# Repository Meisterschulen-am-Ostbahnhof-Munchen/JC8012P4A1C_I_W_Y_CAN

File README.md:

# JC8012P4A1C Enclosure & CAN Addon System

Enclosure, mounting and CAN/Power addon board for the Guition JC8012P4A1C (ESP32-P4, 10.1")
display, used by [espVT](https://github.com/Meisterschulen-am-Ostbahnhof-Munchen/espVT).

The system integrates an ISOBUS/CAN interface, 12 V power supply, a 3D-printed enclosure frame,
and an FR4 backplate with VESA 100 mount and speaker. An optional second variant extends the unit
with a 12-key tactile keypad next to the display.

**Online:** interactive BOMs, schematics and drawings at
<https://meisterschulen-am-ostbahnhof-munchen.github.io/JC8012P4A1C_I_W_Y_CAN/>

More renderings and how they are made: [assembly/render/](assembly/render/README.md).

## Repository Structure

The project is structured into PCBs, mechanics and final assembly:

```text
JC8012P4A1C_I_W_Y_CAN/
├── pcbs/
│   ├── can_power/        # CAN-Bus & 12V/5V power supply addon board
│   ├── backplate/        # FR4 backplate with VESA 100 mount & speaker grille (variant 1)
│   ├── backplate_keypad/ # Widened FR4 backplate for variant 2 (with keypad)
│   └── keypad/           # 12-key tactile keypad PCB (variant 2)
├── mechanics/            # 3D printed frame designs (FreeCAD scripts, STL & STEP files)
├── assembly/             # Assembly drawings (A3 PDF), 3D render models & assembly scripts
├── assembly_bom.csv      # Complete mechanical parts, fasteners & cables BOM
├── mouser_order.csv      # Ordering list for non-Würth components
└── README.md
```

## Variants

| Component | Variant 1 (Standard) | Variant 2 (with Keypad) |
|---|---|---|
| Display | Guition JC8012P4A1C (10.1" ESP32-P4) | Guition JC8012P4A1C (10.1" ESP32-P4) |
| CAN / Power Board | [`pcbs/can_power/`](pcbs/can_power/README.md) | [`pcbs/can_power/`](pcbs/can_power/README.md) |
| Frame | `mechanics/frame.stl` | `mechanics/frame_keypad.stl` |
| Backplate | [`pcbs/backplate/`](pcbs/backplate/README.md) | [`pcbs/backplate_keypad/`](pcbs/backplate_keypad/README.md) (296.9 mm wide) |
| Keypad | — | [`pcbs/keypad/`](pcbs/keypad/README.md) (12 tactile keys F1–F12) |
| Assembly Drawing | [assembly/JC8012P4A1C_assembly_variant1.pdf](assembly/JC8012P4A1C_assembly_variant1.pdf) | [assembly/JC8012P4A1C_assembly_variant2_keypad.pdf](assembly/JC8012P4A1C_assembly_variant2_keypad.pdf) |

Details on mechanics: [mechanics/README.md](mechanics/README.md).  
Details on assembly: [assembly/README.md](assembly/README.md).

## Bills of Materials (BOM)

| BOM | File |
|---|---|
| CAN & Power board | [pcbs/can_power/production/JC8012P4A1C_I_W_Y_CAN_bom.csv](pcbs/can_power/production/JC8012P4A1C_I_W_Y_CAN_bom.csv) |
| Back plate (variant 1) | [pcbs/backplate/production/JC8012P4A1C_backplate_bom.csv](pcbs/backplate/production/JC8012P4A1C_backplate_bom.csv) |
| Back plate (variant 2, keypad) | [pcbs/backplate_keypad/production/JC8012P4A1C_backplate_keypad_bom.csv](pcbs/backplate_keypad/production/JC8012P4A1C_backplate_keypad_bom.csv) |
| Keypad (variant 2) | [pcbs/keypad/production/JC8012P4A1C_keypad_bom.csv](pcbs/keypad/production/JC8012P4A1C_keypad_bom.csv) |
| Final assembly (mechanical fasteners, cables) | [assembly_bom.csv](assembly_bom.csv) |
| Parts to order at Mouser (all non-Würth parts) | [mouser_order.csv](mouser_order.csv) |

### Interactive HTML BOMs (Assembly Checklists)

For manual assembly, interactive HTML BOMs (with checkboxes for soldering and inspection) are provided:

| Board | Interactive BOM |
|---|---|
| CAN & Power board | [pcbs/can_power/production/JC8012P4A1C_I_W_Y_CAN_ibom.html](pcbs/can_power/production/JC8012P4A1C_I_W_Y_CAN_ibom.html) |
| Back plate | [pcbs/backplate/production/JC8012P4A1C_backplate_ibom.html](pcbs/backplate/production/JC8012P4A1C_backplate_ibom.html) |
| Back plate (keypad variant) | [pcbs/backplate_keypad/production/JC8012P4A1C_backplate_keypad_ibom.html](pcbs/backplate_keypad/production/JC8012P4A1C_backplate_keypad_ibom.html) |
| Keypad | [pcbs/keypad/production/JC8012P4A1C_keypad_ibom.html](pcbs/keypad/production/JC8012P4A1C_keypad_ibom.html) |

## Manufacturing

Each PCB folder in `pcbs/` contains its complete KiCad 10 project, local component libraries (`lib/`), documentation (`docs/`), and fabrication outputs (`production/`).
See the respective README files in [`pcbs/can_power/`](pcbs/can_power/README.md), [`pcbs/backplate/`](pcbs/backplate/README.md), [`pcbs/backplate_keypad/`](pcbs/backplate_keypad/README.md), and [`pcbs/keypad/`](pcbs/keypad/README.md) for generation commands and specifications.

The 3D-printable frame is generated using FreeCAD scripts in [`mechanics/`](mechanics/README.md).

## Licence

- Schematics, PCB layouts, scripts and documentation: GPL-3.0 ([LICENSE](LICENSE)).
- `pcbs/*/lib/` and `assembly/models/`: symbols, footprints and 3D models from the Würth Elektronik eiSos libraries, licensed CC BY-SA 4.0 with the Würth exception for designs that use them (see `Wurth_Disclaimer_READ_ME.txt` in these folders).
- Footprints and 3D models from the KiCad standard libraries: CC BY-SA 4.0 with the KiCad exception.
- `mechanics/`: derivative of a Thingiverse design by 8bitmcu, CC BY-SA, see [mechanics/LICENSE.md](mechanics/LICENSE.md).

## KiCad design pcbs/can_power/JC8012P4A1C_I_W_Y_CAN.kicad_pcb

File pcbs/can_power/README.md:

# JC8012P4A1C CAN & Power Board

ISOBUS / CAN interface (250 kbit/s) for the Guition JC8012P4A1C (ESP32-P4, 10.1")
display, used by [espVT](https://github.com/Meisterschulen-am-Ostbahnhof-Munchen/espVT).
The board is mounted on the back of the display board and powered from the 12 V
board net. It also supplies 5 V to the display board.

KiCad 10 project. Project-local libraries are in `lib/`.

Top view: [docs/board_3d_top.png](docs/board_3d_top.png)

## Connections

| Connector | Part | Purpose |
|---|---|---|
| J1 | Würth WR-PHD 610110249121 (2×5 pin header, SMT, right angled) | ribbon cable to IDC D-Sub 9 female Würth 618009221923 |
| J2 | Würth WR-FPC 68711414522 (14 pin, 0.5 mm) | FFC to FPC3 "EXTEND1" of the display board |
| J3 | Würth WR-WTB 653104131822 (4 pin, 1.25 mm) | 5 V to CN2 of the display board |

### D-Sub 9 (via ribbon cable on J1)

Pinout of the Müller-Elektronik BASIC-Terminal CAN-ISO connector. It fits the
adapter cable 481595 (D-Sub 9 male to In-Cab CPC-9 female).

| D-Sub | J1 | Signal |
|---|---|---|
| 1 | 1 | CAN_L |
| 2 | 3 | CAN_L |
| 3 | 5 | TBC_GND (see R8) |
| 4 | 7 | CAN_H |
| 5 | 9 | TBC_PWR_in (not used) |
| 6 | 2 | ECU_GND |
| 7 | 4 | CAN_H |
| 8 | 6 | TBC_PWR_out |
| 9 | 8 | ECU_PWR (12 V board net) |
| – | 10 | not used |

CAN_L (1/2) and CAN_H (4/7) are connected on the board to loop the bus through.

**Polarisation:** J1 has no shroud (an 8 mm high part is the maximum under
the cover, a box header with IDC socket would be too high). To prevent the
IDC socket from being plugged in turned by 180°, cut off pin 10 of J1 and
close position 10 of the IDC socket with a coding plug. Pin 10 is marked
"cut" on the silkscreen. Pins 9 and 10 are
not used. Plugged in turned, the bus TBC_PWR and ECU_PWR (12 V) would end up
on the board GND and CAN_L.

## Mechanics

- All parts on the top side (SMT only), nothing on the bottom side
- Stack height: cover 14 mm − display board 1.5 mm − M2 standoffs 3 mm −
  addon board 1.5 mm ≈ 8 mm free above the addon board
- Fixing on the 58 × 46 mm grid of the display board standoffs S1–S4
  (H1 = S1, H2 = S4, H3 = S2, H4 = S3): SMD steel spacers Würth WA-SMST
  9774025943R (L 2.5 mm, through hole 2.25 mm), land pattern as in the
  datasheet: 5.3 mm GND pad on top, 3.0 mm **non-plated** hole for the
  Ø 2.8 × 1.4 mm collar of the spacer. The DRC rule in
  `JC8012P4A1C_I_W_Y_CAN.kicad_dru` allows the pad right up to the hole.
- Screws **M2×6**, without washer: spacer 2.5 mm + PCB 1.6 mm leaves 1.9 mm
  thread engagement in the 2.5 mm deep blind thread of S1–S4. M2×8 would
  bottom out.
- Notches for CN5 (pin header), the 100 µF capacitor next to S4 and the
  CR1220 RTC holder of the display board

### FPC3 (J2)

| Pin | Signal |
|---|---|
| 1, 2 | GND |
| 7 | CAN_RXD (GPIO5) |
| 8 | CAN_TXD (GPIO4) |
| 9 | CAN_NEN (GPIO3, 10k pull-down: transceiver active by default) |
| 13, 14 | +3V3 (VDDA, transceiver VIO) |

FFC: 14 pin, 0.5 mm pitch, **type B (contacts on opposite sides)**.
The cable leaves FPC3 towards the board edge, makes one 180° turn and enters
J2 from the edge of the addon board. Both connectors are bottom-contact ZIF
with the same orientation (opening towards the edge, pin 1 on the right
side seen from the back of the display, next to the TF card), so pin 1
connects to pin 1. A type A cable would have its contacts facing up at J2;
turning it over to make it fit reverses the pin order and swaps GND (1/2)
and 3V3 (13/14).

## Termination

ISO 11783-2 ECU Type I WEAK: split termination 750 Ω + 750 Ω with 47 nF to GND.

## TBC power output and R8

Like the BASIC-Terminal, the board supplies power for the terminating bias
circuits (TBC) on D-Sub pin 8 (TBC_PWR_out): board net minus about 0.4 V
(Schottky diode D4), limited by PTC F2 (0.14 A). Some harnesses do not start
without it.

**R8 (0 Ω, TBC_GND to GND) is not fitted (DNP) by default.** This keeps
TBC_GND isolated, which is the compatible default. If a harness needs a
TBC_GND return for its terminator, fit R8 with a 0 Ω resistor (0603).

## Power

- 12 V board net only (ECU_PWR), fuse F1 1 A slow
- Bidirectional TVS Würth 824551241 (SMDJ24CA), clamping ≤ 38.9 V
- Reverse polarity protection: dual P-MOSFET Vishay Si4948BEY (SO-8), both
  halves in parallel, 15 V gate zener. Drop-in for the KiCad symbol
  DMP6050SSD (same SO-8 pinout S1 G1 S2 G2 D2 D2 D1 D1), which is used as
  the schematic symbol.
- Buck converter Würth MagI³C 171030601: 5 V / 3 A for the transceiver and the display board

## Test points

SMD pads (1.5 mm), labelled with the net name on the silkscreen:

| TP | Net | Position |
|---|---|---|
| TP1 | +5V | next to J3 |
| TP2 | GND | next to J3 |
| TP3 | CAN_H | between D1 and J1 |
| TP4 | CAN_L | between D1 and J1 |
| TP5 | VIN_PROT (12 V after fuse and reverse polarity protection) | right of C13, below L2 |

## PCB

66 × 54 mm, 1.6 mm, 6 layers:

| Layer | Use |
|---|---|
| F.Cu | all parts and signals, GND pour, local pours for VIN_PROT, VIN_BUCK and +5V |
| In1.Cu | GND plane |
| In2.Cu | +5V plane |
| In3.Cu | GND plane (also balances the copper of In2) |
| In4.Cu | GND plane |
| B.Cu | GND plane, one short signal (CAN_NEN) |

- Vias 0.5 mm / 0.3 mm drill (a 0.2 mm drill costs extra at JLCPCB). Many vias are placed in SMD pads (GND and
  +5V pads, 77 thermal vias under the exposed pad of U2), so the vias
  **must be epoxy filled and capped** (via-in-pad). Without this, solder
  is drawn into the holes during reflow.
- GND stitching vias on a 4 mm grid connect all GND layers.
- Pours connect solid to SMD pads and to the spacer pads H1–H4 (reflow
  soldering, a hand soldering iron will not heat them).
- Net classes: Power 0.8 mm (12 V path and +5V), CAN 0.3 mm, Default 0.25 mm.

## Manufacturing

The current Gerber and drill files are in the zip
`production/JC8012P4A1C_I_W_Y_CAN_gerber.zip` (ready for upload), the BOM
in `production/JC8012P4A1C_I_W_Y_CAN_bom.csv`. Make them again after changes
to the board: in KiCad PCB editor → File → Fabrication Outputs → Gerbers and
Drill Files, or from the command line:

```sh
kicad-cli pcb export gerbers -o production/gerber -l F.Cu,In1.Cu,In2.Cu,In3.Cu,In4.Cu,B.Cu,F.Paste,B.Paste,F.Silkscreen,B.Silkscreen,F.Mask,B.Mask,Edge.Cuts --subtract-soldermask --no-x2 --no-netlist --check-zones JC8012P4A1C_I_W_Y_CAN.kicad_pcb
kicad-cli pcb export drill -o production/gerber/ --format excellon --excellon-units mm --excellon-separate-th JC8012P4A1C_I_W_Y_CAN.kicad_pcb
```

Zip the content of `production/gerber` (the folder itself is not in the
repository) to `production/JC8012P4A1C_I_W_Y_CAN_gerber.zip` and upload it (e.g. JLCPCB:
6 layers, 1.6 mm, via covering "Epoxy Filled & Capped").

Interactive HTML BOM:

```sh
python generate_interactive_bom.py --no-browser --dest-dir production --name-format "%f_ibom" --include-tracks --include-nets --highlight-pin1 all --checkboxes "Gelötet,Kontrolliert" --mark-when-checked "Gelötet" --show-fields "Value,Footprint,MPN" --group-fields "Value,Footprint,MPN" --extra-fields "MPN" --dnp-field kicad_dnp --bom-view left-right --layer-view F --show-fabrication JC8012P4A1C_I_W_Y_CAN.kicad_pcb
```

BOM export:

```sh
kicad-cli sch export bom -o production/JC8012P4A1C_I_W_Y_CAN_bom.csv --fields "Reference,QUANTITY,Value,Manufacturer,MPN,Footprint,DNP" --labels "Reference,Qty,Value,Manufacturer,MPN,Footprint,DNP" --group-by "Value,Footprint,MPN,Manufacturer,DNP" JC8012P4A1C_I_W_Y_CAN.kicad_sch
```

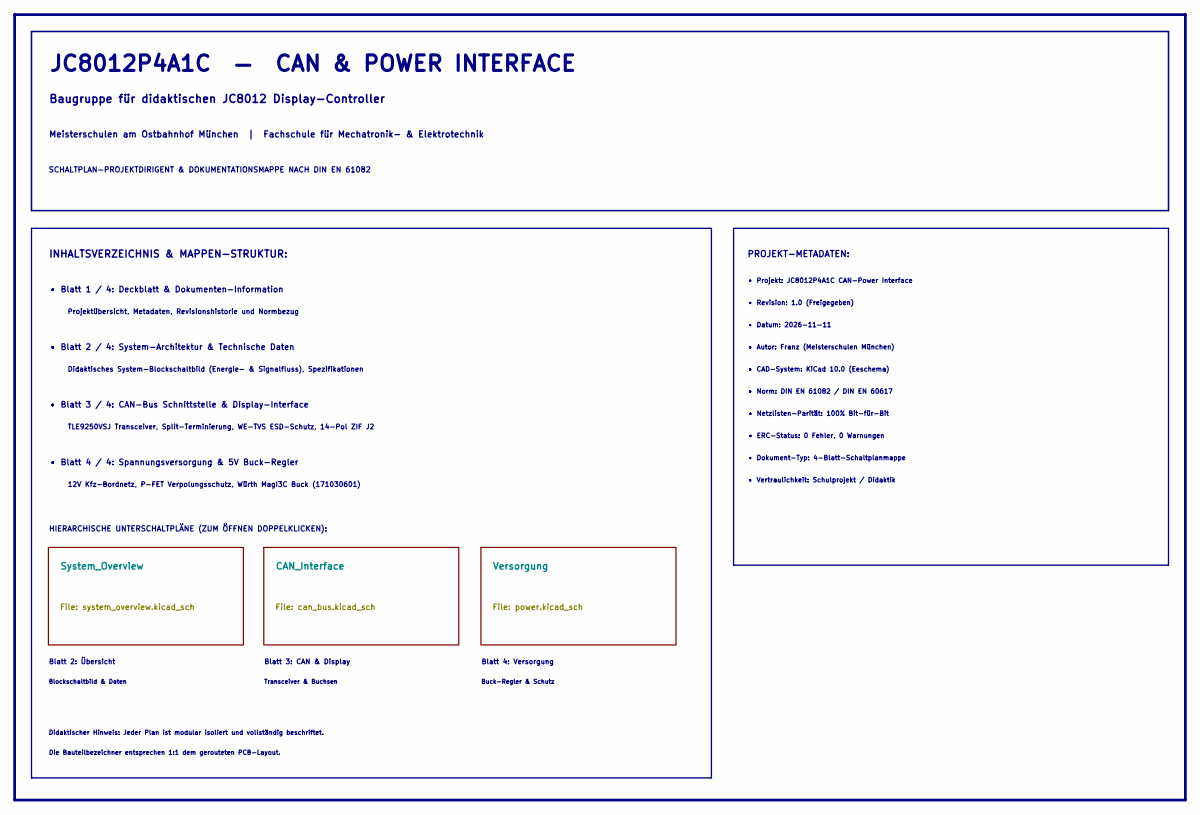
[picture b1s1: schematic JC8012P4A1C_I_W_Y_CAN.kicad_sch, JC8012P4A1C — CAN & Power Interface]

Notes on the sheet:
Projektübersicht, Metadaten, Revisionshistorie und Normbezug
12V Kfz-Bordnetz, P-FET Verpolungsschutz, Würth MagI3C Buck (171030601)
Blatt 2: Übersicht
• CAD-System: KiCad 10.0 (Eeschema)
• Revision: 1.0 (Freigegeben)
HIERARCHISCHE UNTERSCHALTPLÄNE (ZUM ÖFFNEN DOPPELKLICKEN):
Didaktisches System-Blockschaltbild (Energie- & Signalfluss), Spezifikationen
• Netzlisten-Parität: 100% Bit-für-Bit
PROJEKT-METADATEN:
Meisterschulen am Ostbahnhof München | Fachschule für Mechatronik- & Elektrotechnik
• Norm: DIN EN 61082 / DIN EN 60617
• Blatt 3 / 4: CAN-Bus Schnittstelle & Display-Interface
Baugruppe für didaktischen JC8012 Display-Controller
• Dokument-Typ: 4-Blatt-Schaltplanmappe
• ERC-Status: 0 Fehler, 0 Warnungen
Blatt 4: Versorgung
INHALTSVERZEICHNIS & MAPPEN-STRUKTUR:
• Blatt 4 / 4: Spannungsversorgung & 5V Buck-Regler
Buck-Regler & Schutz
• Blatt 2 / 4: System-Architektur & Technische Daten
Blatt 3: CAN & Display
Blockschaltbild & Daten
SCHALTPLAN-PROJEKTDIRIGENT & DOKUMENTATIONSMAPPE NACH DIN EN 61082
• Datum: 2026-11-11
• Vertraulichkeit: Schulprojekt / Didaktik
JC8012P4A1C — CAN & POWER INTERFACE
• Blatt 1 / 4: Deckblatt & Dokumenten-Information
Die Bauteilbezeichner entsprechen 1:1 dem gerouteten PCB-Layout.
Transceiver & Buchsen
TLE9250VSJ Transceiver, Split-Terminierung, WE-TVS ESD-Schutz, 14-Pol ZIF J2
Didaktischer Hinweis: Jeder Plan ist modular isoliert und vollständig beschriftet.
• Autor: Franz (Meisterschulen München)
• Projekt: JC8012P4A1C CAN-Power Interface

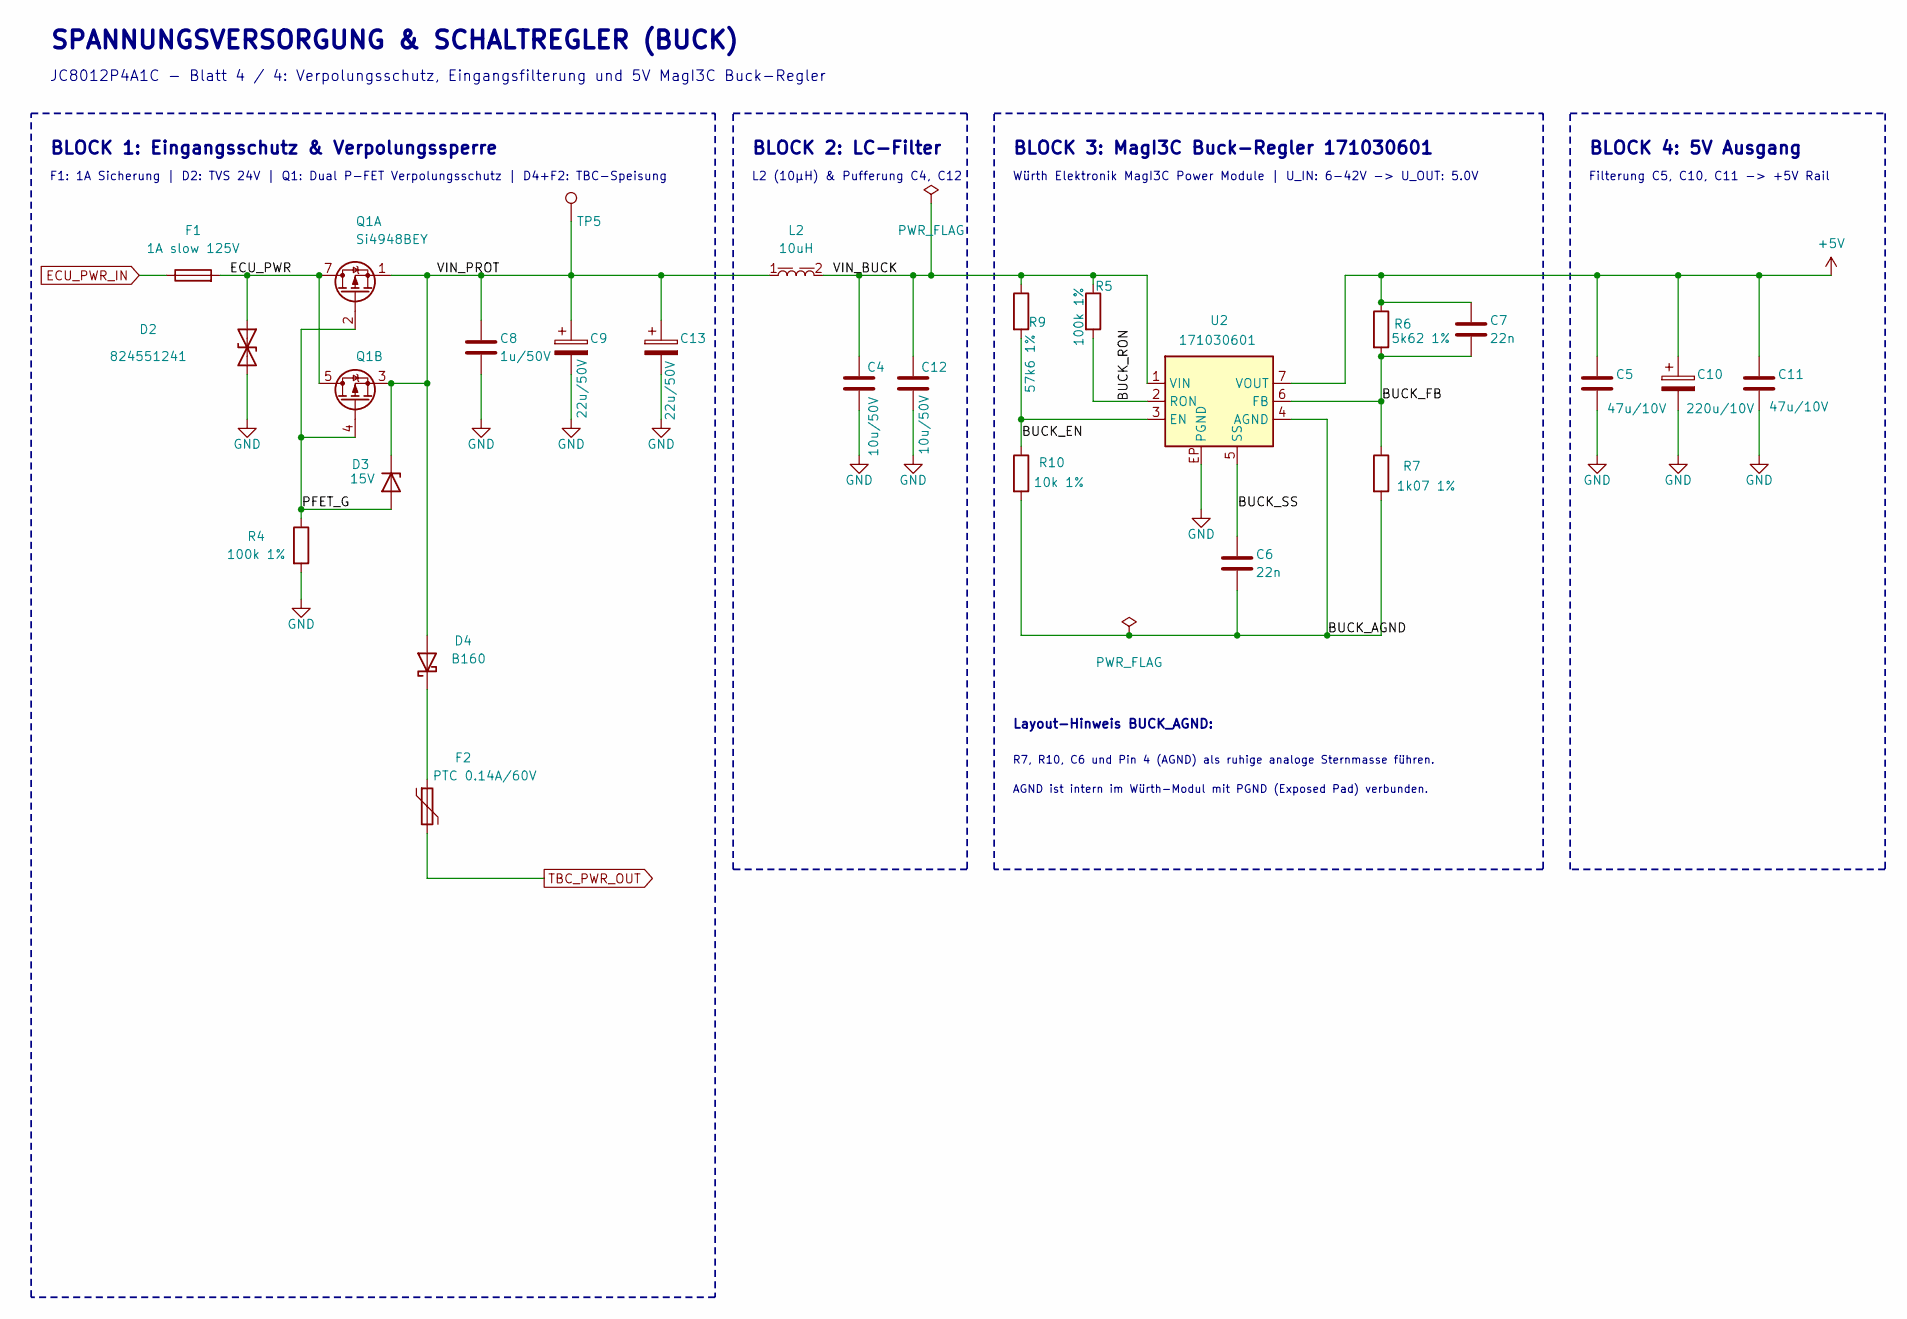
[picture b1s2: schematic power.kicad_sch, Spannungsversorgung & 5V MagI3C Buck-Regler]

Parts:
C4, C12: 10u/50V; C_1210_3225Metric; MPN 885012209073
C5, C11: 47u/10V; C_1210_3225Metric; MPN 885012109007
C6, C7: 22n; C_0603_1608Metric; MPN 885012206091
C8: 1u/50V; C_1210_3225Metric; MPN 885012209047
C9, C13: 22u/50V; CP_Wurth_WCAP-ASLI-D6.3L5.5; MPN 865080643008
C10: 220u/10V; CP_Wurth_WCAP-PSLP-D6.3L5.8; MPN 875105244013
D2: 824551241; D_Wurth_WE-TVSP-DO214-AB-3000W_BI; MPN 824551241
D3: 15V; D_SOD-123; MPN MMSZ5245B_R1_00001
D4: B160; D_SMA; MPN B160-13-F
F1: 1A slow 125V; Fuse_Littelfuse-NANO2-451_453; MPN 0452001.MRL
F2: PTC 0.14A/60V; Fuse_1812_4532Metric; MPN MF-MSMF014-2
L2: 10uH; L_Wurth_WE-PD2-5848; MPN 74477410
Q1: Si4948BEY; SOIC-8_3.9x4.9mm_P1.27mm; MPN SI4948BEY-T1-E3
R4, R5: 100k 1%; R_0603_1608Metric; MPN RC0603FR-07100KL
R6: 5k62 1%; R_0603_1608Metric; MPN RC0603FR-075K62L
R7: 1k07 1%; R_0603_1608Metric; MPN RC0603FR-071K07L
R9: 57k6 1%; R_0603_1608Metric; MPN RC0603FR-0757K6L
R10: 10k 1%; R_0603_1608Metric; MPN RC0603FR-0710KL
TP5: VIN_PROT; TestPoint_Pad_D1.5mm
U2: 171030601; U_Wurth_WPME-VDRM-TO263-7EP; MPN 171030601

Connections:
+5V: C5.1, C7.1, C10.1, C11.1, R6.1, U2.7 (VOUT); also elsewhere on the board
/Versorgung/BUCK_AGND: C6.2, R7.2, R10.2, U2.4 (AGND)
/Versorgung/BUCK_EN: R9.2, R10.1, U2.3 (EN)
/Versorgung/BUCK_FB: C7.2, R6.2, R7.1, U2.6 (FB)
/Versorgung/BUCK_RON: R5.2, U2.2 (RON)
/Versorgung/BUCK_SS: C6.1, U2.5 (SS)
/Versorgung/ECU_PWR: D2.1 (A1), F1.2, Q1.5 (D2), Q1.6 (D2), Q1.7 (D1), Q1.8 (D1)
/Versorgung/PFET_G: D3.2 (A), Q1.2 (G1), Q1.4 (G2), R4.1
/Versorgung/VIN_BUCK: C4.1, C12.1, L2.2, R5.1, R9.1, U2.1 (VIN)
/Versorgung/VIN_PROT: C8.1, C9.1, C13.1, D3.1 (K), D4.2 (A), L2.1, Q1.1 (S1), Q1.3 (S2), TP5.1 (1_1)
unnamed: D4.1 (K), F2.1
TBC_PWR_OUT: F2.2; also elsewhere on the board

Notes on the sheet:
Würth Elektronik MagI3C Power Module | U_IN: 6-42V -> U_OUT: 5.0V
JC8012P4A1C - Blatt 4 / 4: Verpolungsschutz, Eingangsfilterung und 5V MagI3C Buck-Regler
R7, R10, C6 und Pin 4 (AGND) als ruhige analoge Sternmasse führen.
BLOCK 3: MagI3C Buck-Regler 171030601
BLOCK 4: 5V Ausgang
Layout-Hinweis BUCK_AGND:
AGND ist intern im Würth-Modul mit PGND (Exposed Pad) verbunden.
F1: 1A Sicherung | D2: TVS 24V | Q1: Dual P-FET Verpolungsschutz | D4+F2: TBC-Speisung
BLOCK 1: Eingangsschutz & Verpolungssperre
L2 (10µH) & Pufferung C4, C12
Filterung C5, C10, C11 -> +5V Rail
SPANNUNGSVERSORGUNG & SCHALTREGLER (BUCK)
BLOCK 2: LC-Filter

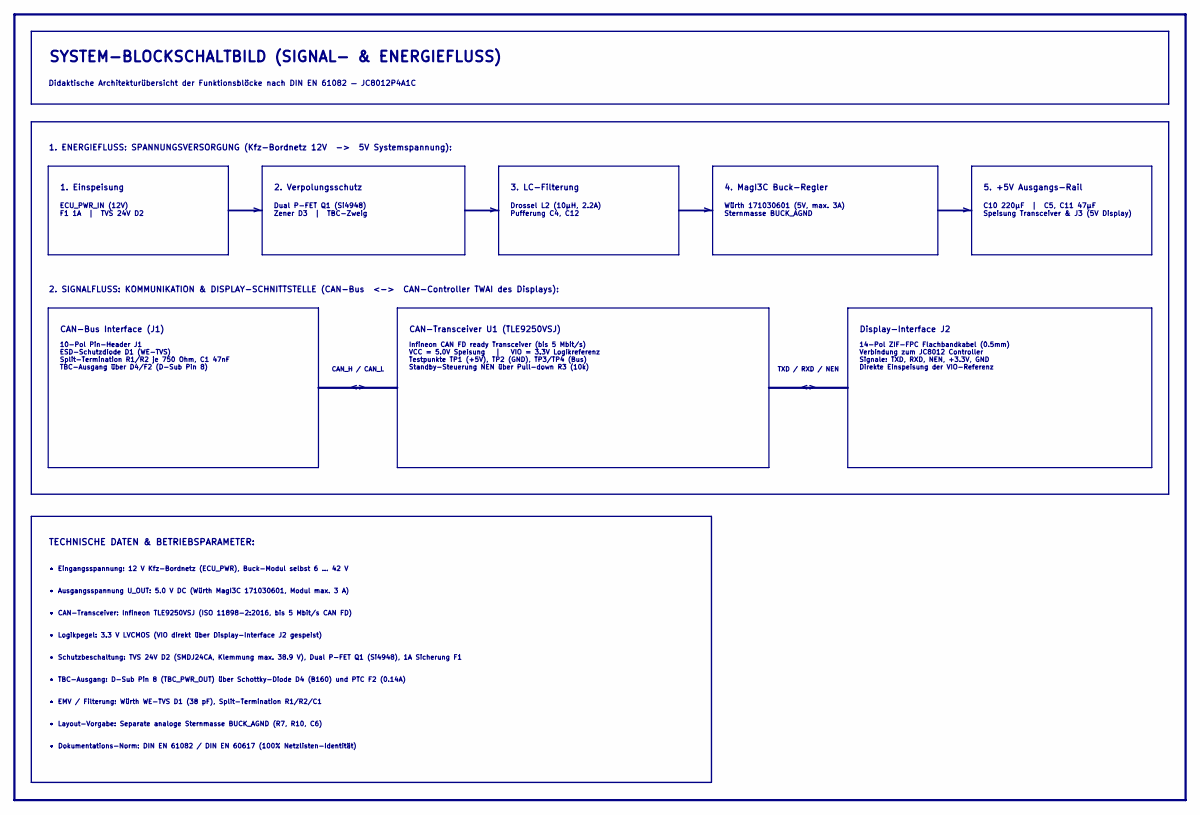
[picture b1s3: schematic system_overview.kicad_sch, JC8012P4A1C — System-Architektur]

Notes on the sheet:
1. Einspeisung
5. +5V Ausgangs-Rail
• Schutzbeschaltung: TVS 24V D2 (SMDJ24CA, Klemmung max. 38.9 V), Dual P-FET Q1 (Si4948), 1A Sicherung F1
TECHNISCHE DATEN & BETRIEBSPARAMETER:
CAN_H / CAN_L
Würth 171030601 (5V, max. 3A) Sternmasse BUCK_AGND
• EMV / Filterung: Würth WE-TVS D1 (38 pF), Split-Termination R1/R2/C1
• Layout-Vorgabe: Separate analoge Sternmasse BUCK_AGND (R7, R10, C6)
• CAN-Transceiver: Infineon TLE9250VSJ (ISO 11898-2:2016, bis 5 Mbit/s CAN FD)
Drossel L2 (10µH, 2.2A) Pufferung C4, C12
Infineon CAN FD ready Transceiver (bis 5 Mbit/s) VCC = 5.0V Speisung | VIO = 3.3V Logikreferenz Testpunkte TP1 (+5V), TP2 (GND), TP3/TP4 (Bus) Standby-Steuerung NEN über Pull-down R3 (10k)
CAN-Transceiver U1 (TLE9250VSJ)
Dual P-FET Q1 (Si4948) Zener D3 | TBC-Zweig
Didaktische Architekturübersicht der Funktionsblöcke nach DIN EN 61082 — JC8012P4A1C
1. ENERGIEFLUSS: SPANNUNGSVERSORGUNG (Kfz-Bordnetz 12V -> 5V Systemspannung):
4. MagI3C Buck-Regler
14-Pol ZIF-FPC Flachbandkabel (0.5mm) Verbindung zum JC8012 Controller Signale: TXD, RXD, NEN, +3.3V, GND Direkte Einspeisung der VIO-Referenz
TXD / RXD / NEN
2. SIGNALFLUSS: KOMMUNIKATION & DISPLAY-SCHNITTSTELLE (CAN-Bus <-> CAN-Controller TWAI des Displays):
3. LC-Filterung
C10 220µF | C5, C11 47µF Speisung Transceiver & J3 (5V Display)
• TBC-Ausgang: D-Sub Pin 8 (TBC_PWR_OUT) über Schottky-Diode D4 (B160) und PTC F2 (0.14A)
• Dokumentations-Norm: DIN EN 61082 / DIN EN 60617 (100% Netzlisten-Identität)
• Logikpegel: 3.3 V LVCMOS (VIO direkt über Display-Interface J2 gespeist)
Display-Interface J2
2. Verpolungsschutz
CAN-Bus Interface (J1)
• Ausgangsspannung U_OUT: 5.0 V DC (Würth MagI3C 171030601, Modul max. 3 A)
ECU_PWR_IN (12V) F1 1A | TVS 24V D2
10-Pol Pin-Header J1 ESD-Schutzdiode D1 (WE-TVS) Split-Termination R1/R2 je 750 Ohm, C1 47nF TBC-Ausgang über D4/F2 (D-Sub Pin 8)
• Eingangsspannung: 12 V Kfz-Bordnetz (ECU_PWR), Buck-Modul selbst 6 ... 42 V
SYSTEM-BLOCKSCHALTBILD (SIGNAL- & ENERGIEFLUSS)

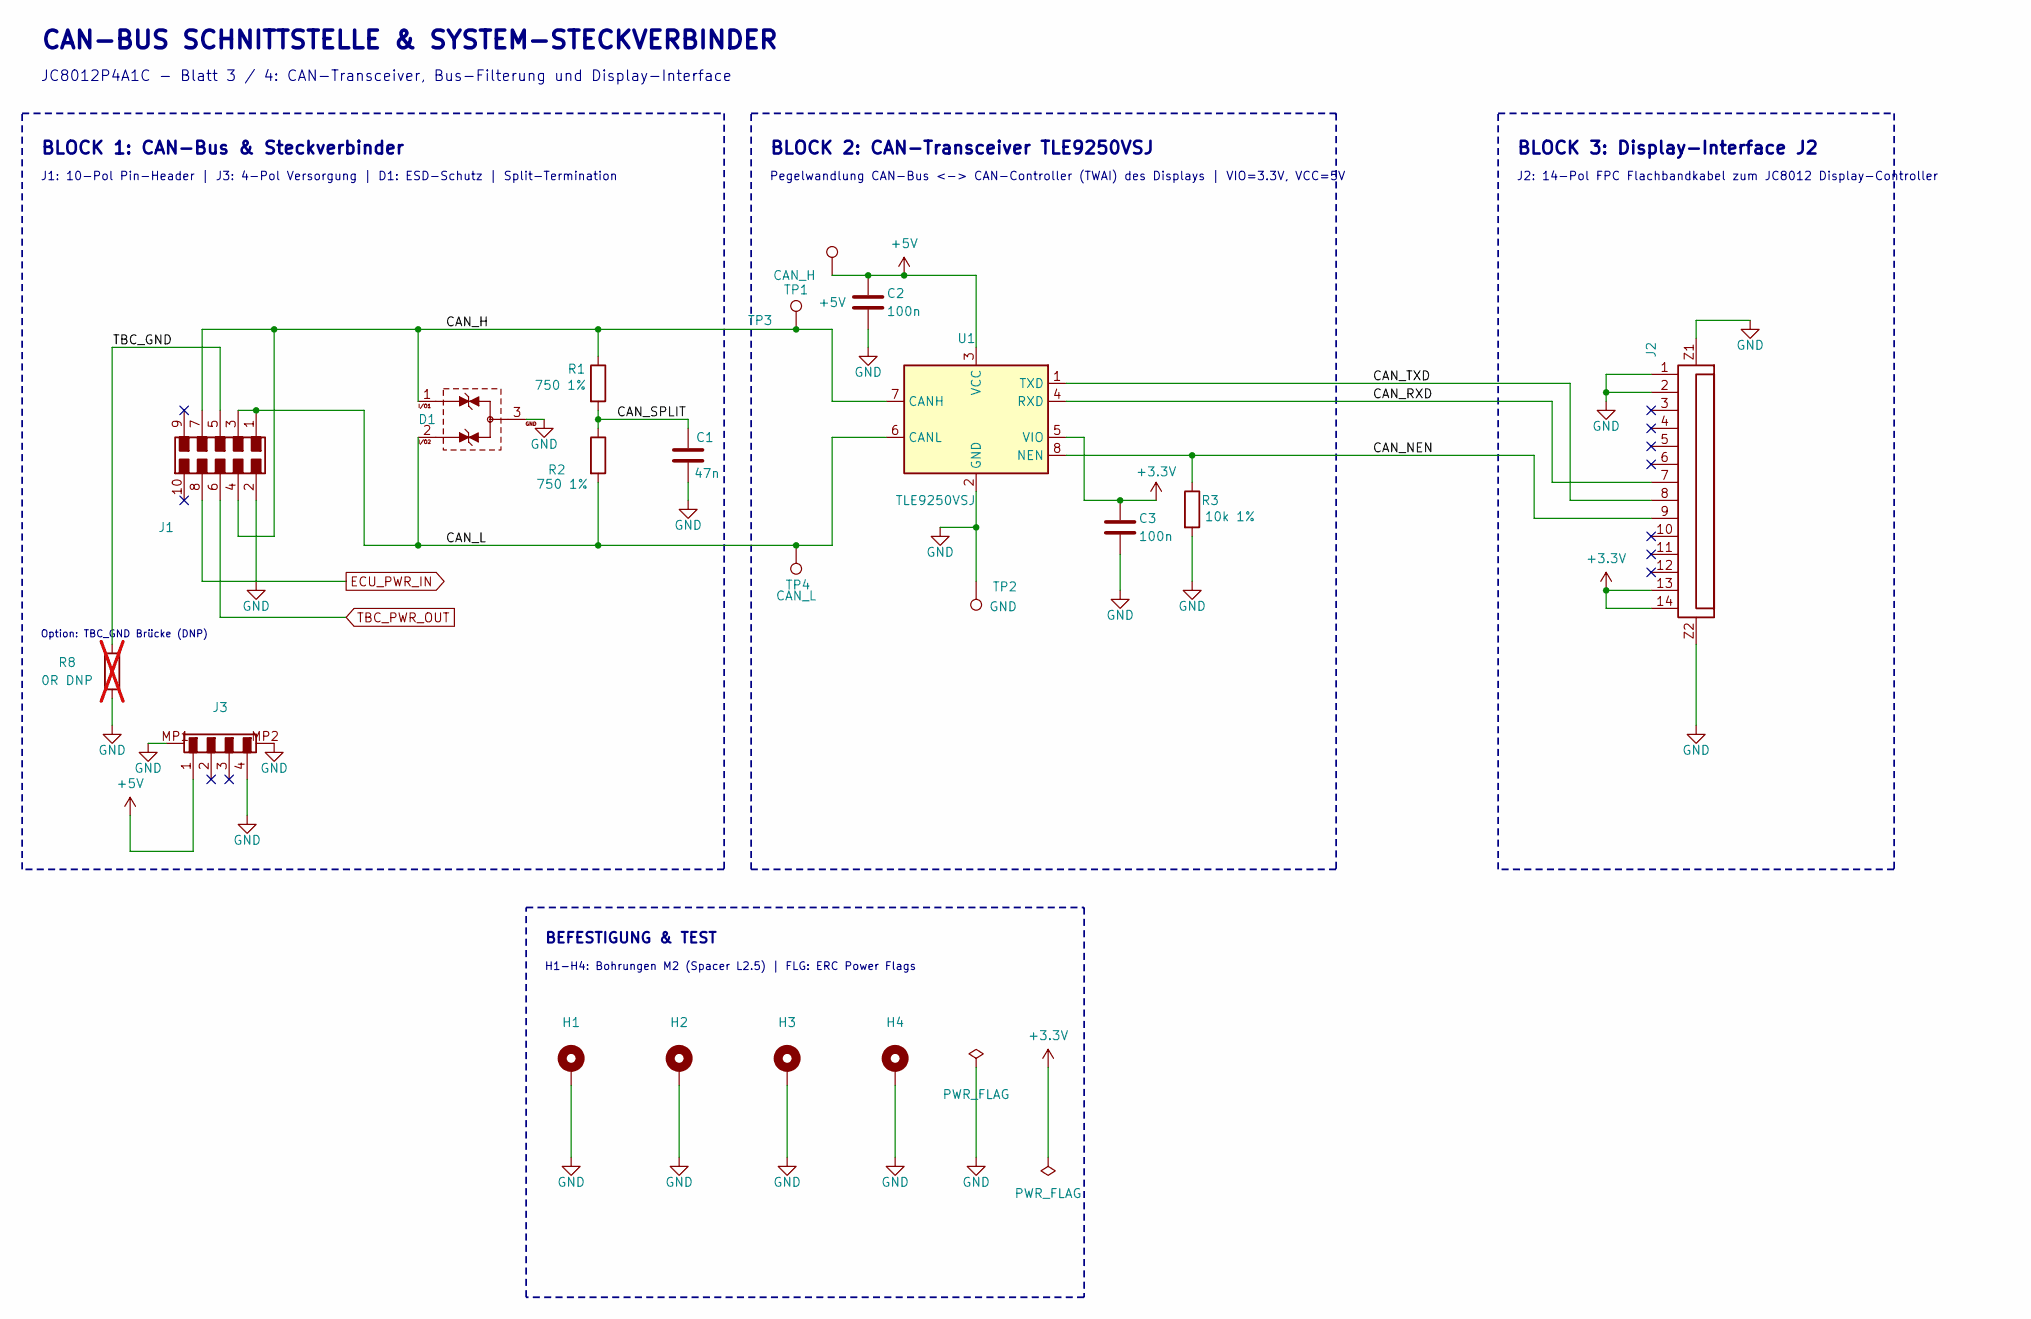
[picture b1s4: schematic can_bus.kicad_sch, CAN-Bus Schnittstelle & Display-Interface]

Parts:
C1: 47n; C_0603_1608Metric; MPN 885012206093
C2, C3: 100n; C_0603_1608Metric; MPN 885012206095
D1: 824094024; D_Wurth_WE-TVS-SOT23-3L; MPN 824094024
H1, H2, H3, H4: Spacer M2 L2.5; A_Wurth_WA-SMST_9774025943R; MPN 9774025943R
J1: 610110249121; J_Wurth_WR-PHD_610110249121; MPN 610110249121
J2: 68711414522; J_Wurth_WR-FPC_68711414522; MPN 68711414522
J3: 653104131822; J_Wurth_WR-WTB_653104131822; MPN 653104131822
R1, R2: 750 1%; R_1206_3216Metric; MPN RC1206FR-07750RL
R3: 10k 1%; R_0603_1608Metric; MPN RC0603FR-0710KL
R8: 0R DNP; R_0603_1608Metric; MPN RC0603JR-070RL; not fitted
TP1: +5V; TestPoint_Pad_D1.5mm
TP2: GND; TestPoint_Pad_D1.5mm
TP3: CAN_H; TestPoint_Pad_D1.5mm
TP4: CAN_L; TestPoint_Pad_D1.5mm
U1: TLE9250VSJ; SOIC-8_3.9x4.9mm_P1.27mm; MPN TLE9250VSJXUMA1

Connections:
+3.3V: C3.1, J2.13, J2.14, U1.5 (VIO)
+5V: C2.1, J3.1, TP1.1 (1_1), U1.3 (VCC); also elsewhere on the board
/CAN_Interface/CAN_H: D1.1 (I/O1), J1.4, J1.7, R1.1, TP3.1 (1_1), U1.7 (CANH)
/CAN_Interface/CAN_L: D1.2 (I/O2), J1.1, J1.3, R2.2, TP4.1 (1_1), U1.6 (CANL)
/CAN_Interface/CAN_NEN: J2.9, R3.1, U1.8 (NEN)
/CAN_Interface/CAN_RXD: J2.7, U1.4 (RXD)
/CAN_Interface/CAN_SPLIT: C1.1, R1.2, R2.1
/CAN_Interface/CAN_TXD: J2.8, U1.1 (TXD)
/CAN_Interface/TBC_GND: J1.5, R8.1
TBC_PWR_OUT: J1.6; also elsewhere on the board

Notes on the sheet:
Pegelwandlung CAN-Bus <-> CAN-Controller (TWAI) des Displays | VIO=3.3V, VCC=5V
JC8012P4A1C - Blatt 3 / 4: CAN-Transceiver, Bus-Filterung und Display-Interface
H1-H4: Bohrungen M2 (Spacer L2.5) | FLG: ERC Power Flags
BEFESTIGUNG & TEST
BLOCK 1: CAN-Bus & Steckverbinder
BLOCK 2: CAN-Transceiver TLE9250VSJ
J2: 14-Pol FPC Flachbandkabel zum JC8012 Display-Controller
BLOCK 3: Display-Interface J2
Option: TBC_GND Brücke (DNP)
CAN-BUS SCHNITTSTELLE & SYSTEM-STECKVERBINDER
J1: 10-Pol Pin-Header | J3: 4-Pol Versorgung | D1: ESD-Schutz | Split-Termination

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
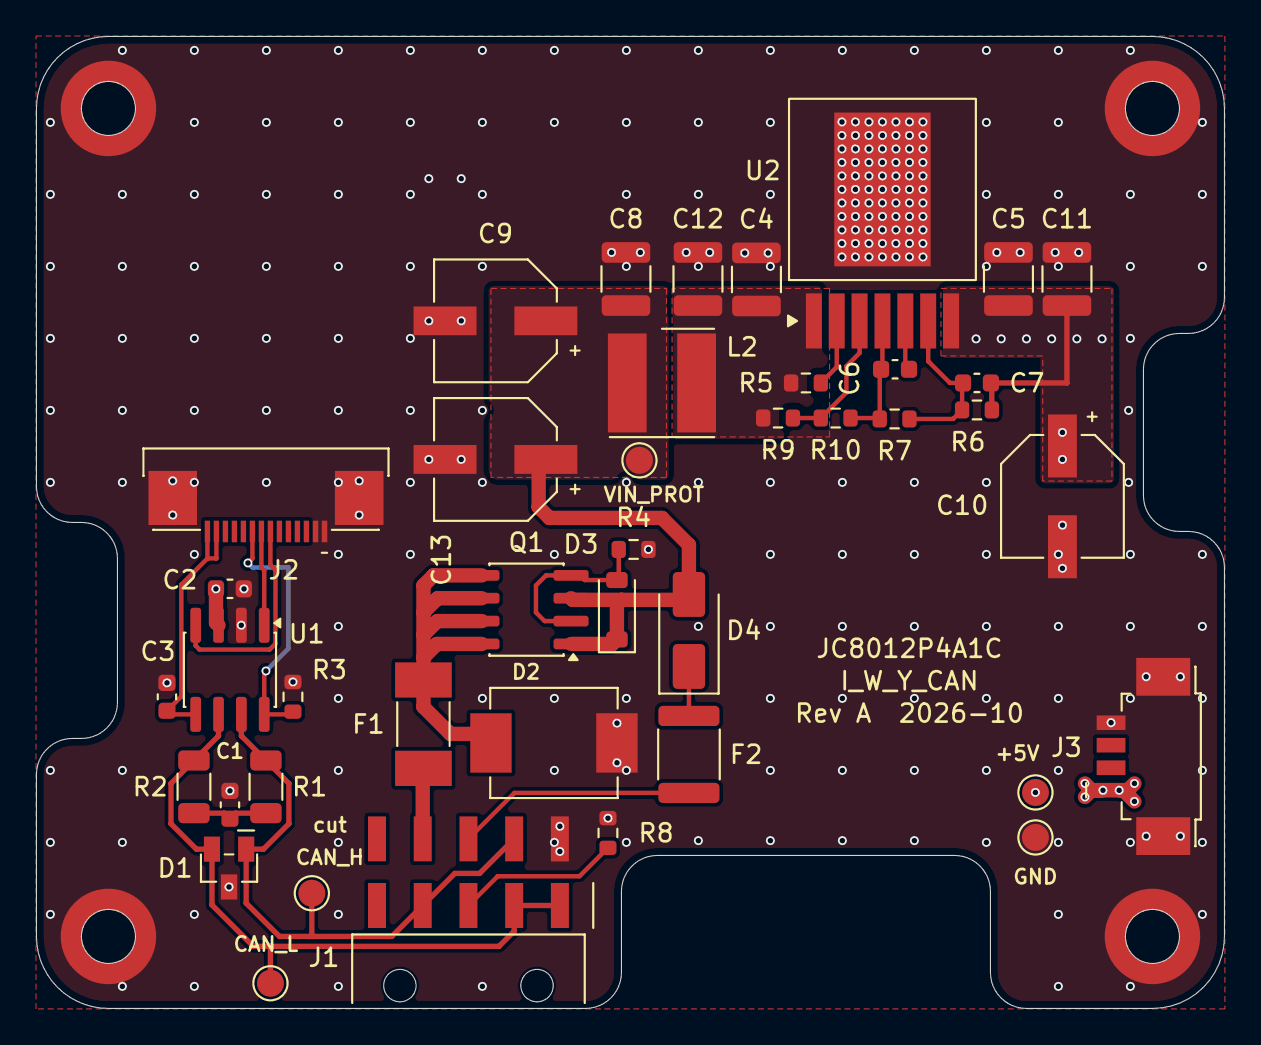
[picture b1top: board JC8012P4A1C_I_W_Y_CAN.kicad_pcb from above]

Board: 6 copper layers, 66.0 x 54.0 mm, 45 parts (0 on the bottom side), 22 nets.

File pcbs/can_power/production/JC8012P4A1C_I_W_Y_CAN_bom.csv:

"Reference","Qty","Value","Manufacturer","MPN","Footprint","DNP"
"C1","1","47n","Wurth Elektronik","885012206093","Capacitor_SMD:C_0603_1608Metric",""
"C2,C3","2","100n","Wurth Elektronik","885012206095","Capacitor_SMD:C_0603_1608Metric",""
"C4,C12","2","10u/50V","Wurth Elektronik","885012209073","Capacitor_SMD:C_1210_3225Metric",""
"C5,C11","2","47u/10V","Wurth Elektronik","885012109007","Capacitor_SMD:C_1210_3225Metric",""
"C6,C7","2","22n","Wurth Elektronik","885012206091","Capacitor_SMD:C_0603_1608Metric",""
"C8","1","1u/50V","Wurth Elektronik","885012209047","Capacitor_SMD:C_1210_3225Metric",""
"C9,C13","2","22u/50V","Wurth Elektronik","865080643008","JC8012P4A1C_CAN:CP_Wurth_WCAP-ASLI-D6.3L5.5",""
"C10","1","220u/10V","Wurth Elektronik","875105244013","JC8012P4A1C_CAN:CP_Wurth_WCAP-PSLP-D6.3L5.8",""
"D1","1","824094024","Wurth Elektronik","824094024","JC8012P4A1C_CAN:D_Wurth_WE-TVS-SOT23-3L",""
"D2","1","824551241","Wurth Elektronik","824551241","JC8012P4A1C_CAN:D_Wurth_WE-TVSP-DO214-AB-3000W_BI",""
"D3","1","15V","Panjit","MMSZ5245B_R1_00001","Diode_SMD:D_SOD-123",""
"D4","1","B160","Diodes Incorporated","B160-13-F","Diode_SMD:D_SMA",""
"F1","1","1A slow 125V","Littelfuse","0452001.MRL","Fuse:Fuse_Littelfuse-NANO2-451_453",""
"F2","1","PTC 0.14A/60V","Bourns","MF-MSMF014-2","Fuse:Fuse_1812_4532Metric",""
"H1-H4","4","Spacer M2 L2.5","Wurth Elektronik","9774025943R","JC8012P4A1C_CAN:A_Wurth_WA-SMST_9774025943R",""
"J1","1","610110249121","Wurth Elektronik","610110249121","JC8012P4A1C_CAN:J_Wurth_WR-PHD_610110249121",""
"J2","1","68711414522","Wurth Elektronik","68711414522","JC8012P4A1C_CAN:J_Wurth_WR-FPC_68711414522",""
"J3","1","653104131822","Wurth Elektronik","653104131822","JC8012P4A1C_CAN:J_Wurth_WR-WTB_653104131822",""
"L2","1","10uH","Wurth Elektronik","74477410","JC8012P4A1C_CAN:L_Wurth_WE-PD2-5848",""
"Q1","1","Si4948BEY","Vishay","SI4948BEY-T1-E3","Package_SO:SOIC-8_3.9x4.9mm_P1.27mm",""
"R1,R2","2","750 1%","Yageo","RC1206FR-07750RL","Resistor_SMD:R_1206_3216Metric",""
"R3,R10","2","10k 1%","Yageo","RC0603FR-0710KL","Resistor_SMD:R_0603_1608Metric",""
"R4,R5","2","100k 1%","Yageo","RC0603FR-07100KL","Resistor_SMD:R_0603_1608Metric",""
"R6","1","5k62 1%","Yageo","RC0603FR-075K62L","Resistor_SMD:R_0603_1608Metric",""
"R7","1","1k07 1%","Yageo","RC0603FR-071K07L","Resistor_SMD:R_0603_1608Metric",""
"R8","1","0R DNP","Yageo","RC0603JR-070RL","Resistor_SMD:R_0603_1608Metric","Nicht bestücken"
"R9","1","57k6 1%","Yageo","RC0603FR-0757K6L","Resistor_SMD:R_0603_1608Metric",""
"U1","1","TLE9250VSJ","Infineon","TLE9250VSJXUMA1","Package_SO:SOIC-8_3.9x4.9mm_P1.27mm",""
"U2","1","171030601","Wurth Elektronik","171030601","JC8012P4A1C_CAN:U_Wurth_WPME-VDRM-TO263-7EP",""

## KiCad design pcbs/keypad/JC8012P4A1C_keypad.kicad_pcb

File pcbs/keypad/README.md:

# JC8012P4A1C keypad (variant 2)

Keypad with 12 keys (2 columns x 6 rows) right of the display, seen from the
**front**. KiCad 10 project. Used together with the frame `../../mechanics/frame_keypad.stl`
and the wide back plate `../backplate_keypad`.

| front (keys) | back (J1) |
|---|---|
|  |  |

## Sandwich

Same principle as the 4 key board `ISOBUS_Hardware/XL-accessories/Board_4_Buttons`
(Folika FO SON PU 005):

| Layer | Thickness |
|---|---|
| PU foil, printed, 3M 468MP adhesive, no adhesive in the key fields | rest |
| plexiglass 3 mm with pockets for the keys, 3M 300LSE adhesive | 3.0 mm + adhesive |
| PCB FR4 | 1.6 mm |
| **total (flat part, measured at the edge)** | **5.5 mm** |

- Outline 48 x 150 mm, corner radius 1.5 mm, the same for foil, plexiglass and PCB.
- Plexiglass: 16.3 x 16.3 mm pockets for the keys (key 12 mm, enlarged for the
  solder tabs), dia 6.6 mm holes for the spacers H1-H4. Each pocket has a notch
  5.8 x 1.45 mm for the diode (notch centre 3.5 mm from the key centre towards
  the outer edge, notch edge 9.6 mm from the key centre). Top row: notch below
  the key, all other rows: above the key, so the notch keeps away from the
  spacer holes.
- The actuator (4.3 mm above the PCB) pushes the foil about 0.4 mm outwards,
  as on the 4 key board.
- Print in the style of FO SON PU 005: light grey background (2 mm bleed),
  14 mm key fields in colour with a 2 mm grey frame, labels F1-F12 in Arial Bold,
  school logo below the keys.
- Cutting drawing for Folika (1:1, A4) and DXF:
  [docs/folika_keypad_12.pdf](docs/folika_keypad_12.pdf),
  [docs/folika_keypad_12.dxf](docs/folika_keypad_12.dxf).

## Mounting in the frame

- The sandwich lies in a pocket of the frame. The foil is **2 mm behind the
  glass front** of the display (z = 23 in frame coordinates, glass z = 25), the
  domes over the actuators stay about 1.5 mm behind the glass plane, so nothing
  is pressed when the unit lies on its front. The frame edge protects the edge
  of the foil.
- The back of the PCB rests on a ledge of the frame (z = 17.5).
- H1-H4: Wurth WA-SMSI 9774030151R, SMD steel spacers M2.5, L 3 mm, soldered on
  the front side in the same reflow run as the keys. They sit in the holes of
  the plexiglass, 0.1 mm or more below the foil.
- Screws **M2.5 x 8** from behind through the 4 mm lugs of the frame and the PCB
  into the spacers (2.4 mm thread). **Do not use longer screws**, an M2.5 x 10
  pushes through the foil. Max. 0.35 Nm (spacer). The same screw is used for
  the speaker.
- The key forces go into the ledge, the screws only hold the sandwich.

## Electrics

Schematic: 3 sheets (cover sheet, overview with key table, matrix with J1),
PDF: [docs/JC8012P4A1C_keypad_schematic.pdf](docs/JC8012P4A1C_keypad_schematic.pdf).

3 x 4 key matrix with one diode per key (no ghost keys, any number of keys at
the same time), read by the component
[keyboard_button](https://docs.espressif.com/projects/esp-iot-solution/en/latest/input_device/keyboard_button.html)
of esp-iot-solution: the outputs drive high one after another, the inputs use
the internal pull-down (`active_level = 1`). No LEDs, no supply needed on the
keypad.

J1 (Wurth WR-FPC 68711414522, 14 pin, 0.5 mm, on the **back** side, at the top
edge) -> FFC -> FPC4 "EXTEND2" of the display board. FPC4 carries GPIO28-34 on
pins 6-12 (none of them has an ADC, so a resistor ladder is not possible).
The GPIO list below is only valid with a cable that connects pin n to pin n.

| J1 / FPC4 pin | GPIO | Net | Use |
|---|---|---|---|
| 1, 2 | GND | - | not used |
| 3, 4, 5 | - | - | not connected on the display board |
| 6 | GPIO28 | IN0 | input |
| 7 | GPIO29 | IN2 | input |
| 8 | GPIO30 | OUT1 | output |
| 9 | GPIO31 | OUT0 | output |
| 10 | GPIO32 | OUT2 | output |
| 11 | GPIO33 | IN3 | input |
| 12 | GPIO34 | IN1 | input (strapping pin for the JTAG source, only with eFuse, not set by default) |
| 13, 14 | VDDA | - | not used |

```c
keyboard_btn_config_t cfg = {
    .output_gpios = (int[]){31, 30, 32},       // OUT0, OUT1, OUT2
    .output_gpio_num = 3,
    .input_gpios = (int[]){28, 34, 29, 33},    // IN0, IN1, IN2, IN3
    .input_gpio_num = 4,
    .active_level = 1,
    .debounce_ticks = 2,
    .ticks_interval = 500,
    .enable_power_save = false,
};
```

Key numbering as on the CCI 60 terminal, seen from the front: F1-F6 in the
outer (right) column, F7-F12 in the column next to the display, each top to
bottom. The reference designators follow it: Sn is key Fn, Dn its diode.

| Row | left column, next to the display | right column, outer |
|---|---|---|
| 1 | F7 OUT0 / IN0 | F1 OUT0 / IN1 |
| 2 | F8 OUT0 / IN2 | F2 OUT0 / IN3 |
| 3 | F9 OUT1 / IN0 | F3 OUT1 / IN1 |
| 4 | F10 OUT1 / IN2 | F4 OUT1 / IN3 |
| 5 | F11 OUT2 / IN0 | F5 OUT2 / IN1 |
| 6 | F12 OUT2 / IN2 | F6 OUT2 / IN3 |

Key pitch 22.56 mm vertical (active area of the LCD 135.36 mm / 6, so every key
is level with one soft key field of the screen) and 24 mm horizontal.

## PCB

48 x 150 mm, 1.6 mm, 2 layers. Keys, diodes and spacers on the front (F),
only J1 on the back (B). Tracks 0.25 mm (0.2 mm at J1) with 45° corners, vias 0.6 / 0.3 mm.
The diodes (SOD-123) sit next to each key, in the notches of the plexiglass pockets
(above the key, below it in the top row). Top row: the diode is on pads 3/4
and the input on pads 1/2, the other rows the other way round.

## Parts

[production/JC8012P4A1C_keypad_bom.csv](production/JC8012P4A1C_keypad_bom.csv),
interactive BOM [production/JC8012P4A1C_keypad_ibom.html](production/JC8012P4A1C_keypad_ibom.html).

| Ref | Part |
|---|---|
| S1-S12 | Wurth WS-TASV 430162043826, SMT tact switch 12 x 12 mm, H 4.3 mm, 260 g |
| D1-D12 | Panjit BAT43W_R1_00001, Schottky diode 30 V 200 mA, SOD-123 (Mouser 241-BAT43W_R1_00001) |
| H1-H4 | Wurth WA-SMSI 9774030151R, M2.5, L 3 mm |
| J1 | Wurth WR-FPC 68711414522 |

## Manufacturing

Gerber and drill files: `production/JC8012P4A1C_keypad_gerber.zip`
(2 layers, 1.6 mm). Stencil for the **top side** (keys, diodes, spacers). J1 on
the back is soldered by hand afterwards (it sits at the edge). Commands as for
the back plate (see `../backplate/README.md`), with the project name
`JC8012P4A1C_keypad`.

## Open points

- FFC: 14 pin, 0.5 mm, about 250 mm. The cable runs from FPC4 through the slot
  in the display cover, along the top of the frame, through the slot in the
  side wall into the chamber and enters J1 from the top edge. Check length and
  type (contacts on the same side or opposite sides) with a paper strip on the
  test print: pin 1 must end on pin 1, otherwise the GPIO list above is wrong.
- Colour of the key fields on the foil: one blue for all keys for now.

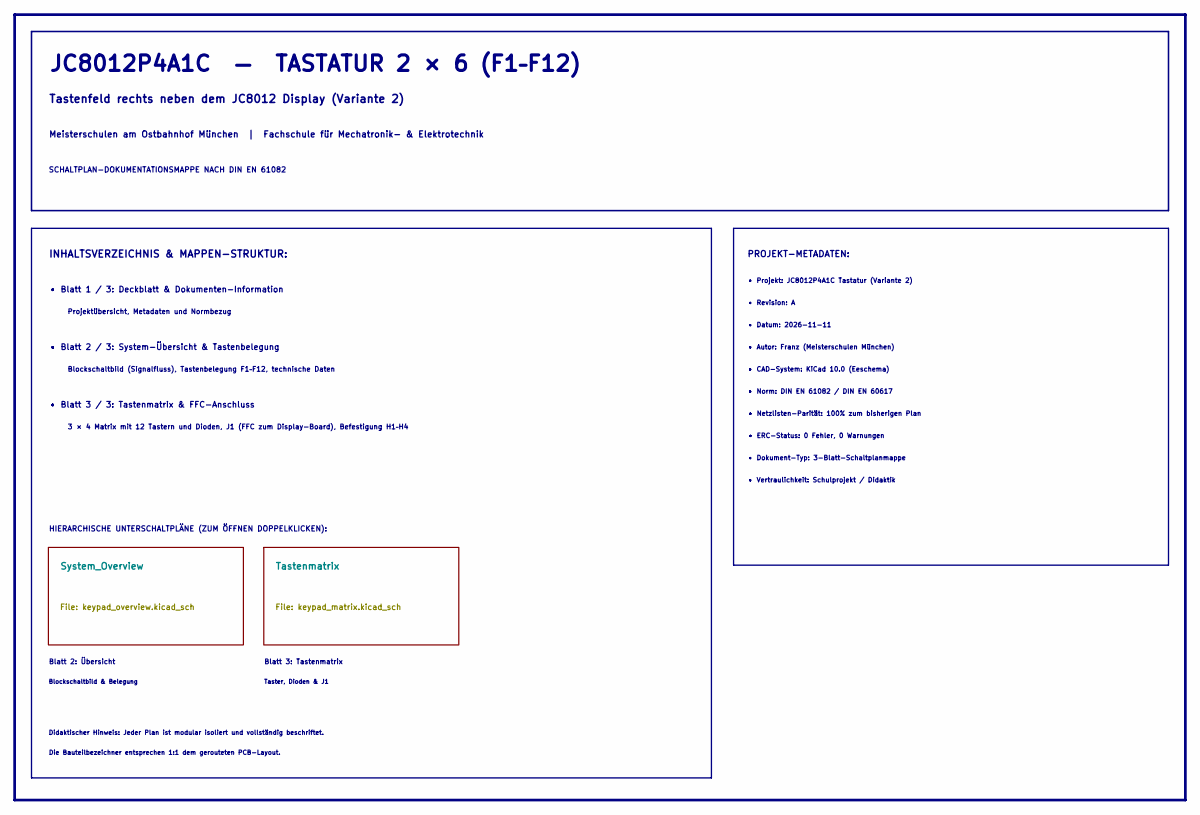
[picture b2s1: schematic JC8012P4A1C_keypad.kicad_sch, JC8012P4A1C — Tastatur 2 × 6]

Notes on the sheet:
SCHALTPLAN-DOKUMENTATIONSMAPPE NACH DIN EN 61082
Projektübersicht, Metadaten und Normbezug
• Norm: DIN EN 61082 / DIN EN 60617
Didaktischer Hinweis: Jeder Plan ist modular isoliert und vollständig beschriftet.
• Blatt 3 / 3: Tastenmatrix & FFC-Anschluss
• Netzlisten-Parität: 100% zum bisherigen Plan
• Datum: 2026-11-11
Blatt 2: Übersicht
Blockschaltbild (Signalfluss), Tastenbelegung F1–F12, technische Daten
JC8012P4A1C — TASTATUR 2 × 6 (F1–F12)
• Revision: A
Blockschaltbild & Belegung
• Vertraulichkeit: Schulprojekt / Didaktik
• CAD-System: KiCad 10.0 (Eeschema)
PROJEKT-METADATEN:
• ERC-Status: 0 Fehler, 0 Warnungen
• Dokument-Typ: 3-Blatt-Schaltplanmappe
Tastenfeld rechts neben dem JC8012 Display (Variante 2)
• Projekt: JC8012P4A1C Tastatur (Variante 2)
• Autor: Franz (Meisterschulen München)
• Blatt 1 / 3: Deckblatt & Dokumenten-Information
Die Bauteilbezeichner entsprechen 1:1 dem gerouteten PCB-Layout.
• Blatt 2 / 3: System-Übersicht & Tastenbelegung
Blatt 3: Tastenmatrix
Meisterschulen am Ostbahnhof München | Fachschule für Mechatronik- & Elektrotechnik
HIERARCHISCHE UNTERSCHALTPLÄNE (ZUM ÖFFNEN DOPPELKLICKEN):
INHALTSVERZEICHNIS & MAPPEN-STRUKTUR:
3 × 4 Matrix mit 12 Tastern und Dioden, J1 (FFC zum Display-Board), Befestigung H1–H4
Taster, Dioden & J1

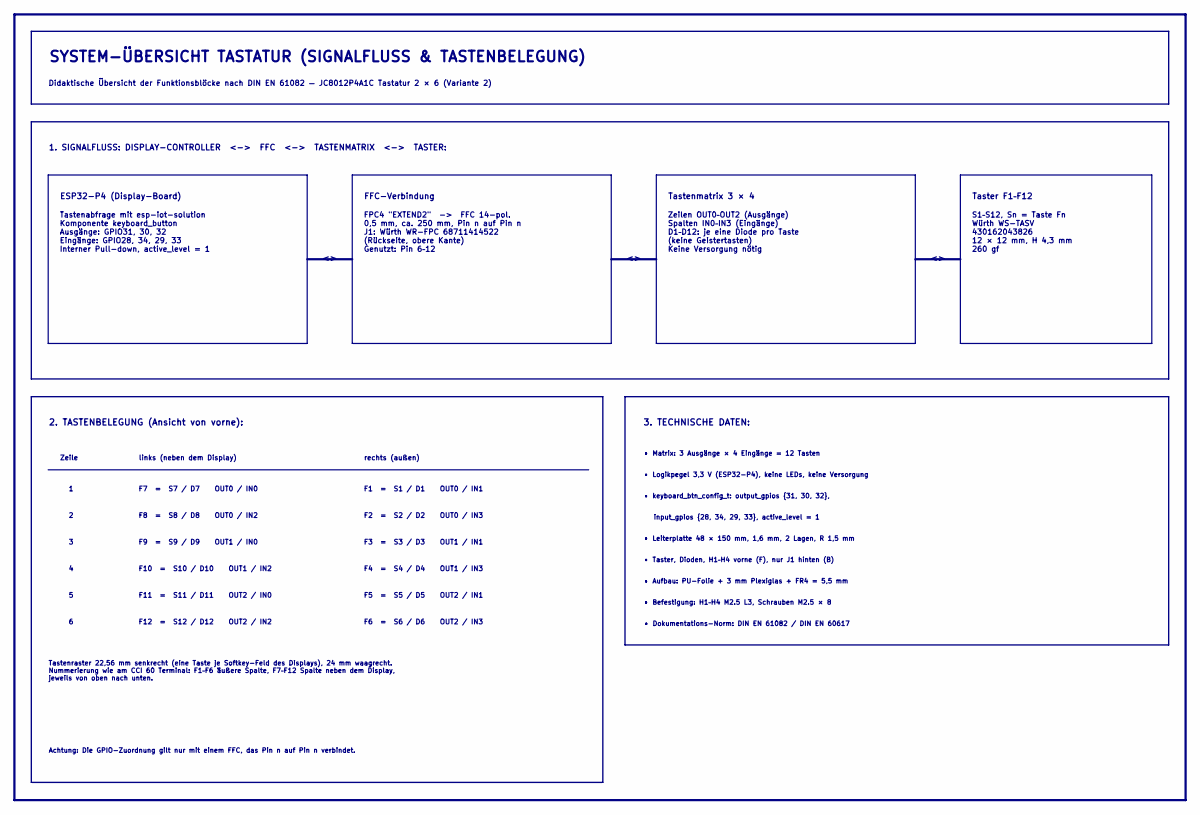
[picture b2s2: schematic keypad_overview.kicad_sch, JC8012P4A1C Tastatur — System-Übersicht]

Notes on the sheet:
• Befestigung: H1–H4 M2.5 L3, Schrauben M2.5 × 8
FPC4 "EXTEND2" -> FFC 14-pol. 0,5 mm, ca. 250 mm, Pin n auf Pin n J1: Würth WR-FPC 68711414522 (Rückseite, obere Kante) Genutzt: Pin 6–12
2. TASTENBELEGUNG (Ansicht von vorne):
F6 = S6 / D6 OUT2 / IN3
F3 = S3 / D3 OUT1 / IN1
Tastenraster 22,56 mm senkrecht (eine Taste je Softkey-Feld des Displays), 24 mm waagrecht. Nummerierung wie am CCI 60 Terminal: F1–F6 äußere Spalte, F7–F12 Spalte neben dem Display, jeweils von oben nach unten.
1. SIGNALFLUSS: DISPLAY-CONTROLLER <-> FFC <-> TASTENMATRIX <-> TASTER:
• keyboard_btn_config_t: output_gpios {31, 30, 32},
• Logikpegel 3,3 V (ESP32-P4), keine LEDs, keine Versorgung
Zeilen OUT0–OUT2 (Ausgänge) Spalten IN0–IN3 (Eingänge) D1–D12: je eine Diode pro Taste (keine Geistertasten) Keine Versorgung nötig
F5 = S5 / D5 OUT2 / IN1
F11 = S11 / D11 OUT2 / IN0
F9 = S9 / D9 OUT1 / IN0
F1 = S1 / D1 OUT0 / IN1
links (neben dem Display)
S1–S12, Sn = Taste Fn Würth WS-TASV 430162043826 12 × 12 mm, H 4,3 mm 260 gf
F12 = S12 / D12 OUT2 / IN2
Zeile
FFC-Verbindung
F4 = S4 / D4 OUT1 / IN3
• Leiterplatte 48 × 150 mm, 1,6 mm, 2 Lagen, R 1,5 mm
• Aufbau: PU-Folie + 3 mm Plexiglas + FR4 = 5,5 mm
F8 = S8 / D8 OUT0 / IN2
• Taster, Dioden, H1–H4 vorne (F), nur J1 hinten (B)
Achtung: Die GPIO-Zuordnung gilt nur mit einem FFC, das Pin n auf Pin n verbindet.
F2 = S2 / D2 OUT0 / IN3
Tastenmatrix 3 × 4
3. TECHNISCHE DATEN:
rechts (außen)
SYSTEM-ÜBERSICHT TASTATUR (SIGNALFLUSS & TASTENBELEGUNG)
• Matrix: 3 Ausgänge × 4 Eingänge = 12 Tasten
input_gpios {28, 34, 29, 33}, active_level = 1
Tastenabfrage mit esp-iot-solution Komponente keyboard_button Ausgänge: GPIO31, 30, 32 Eingänge: GPIO28, 34, 29, 33 Interner Pull-down, active_level = 1
F10 = S10 / D10 OUT1 / IN2
• Dokumentations-Norm: DIN EN 61082 / DIN EN 60617
Didaktische Übersicht der Funktionsblöcke nach DIN EN 61082 — JC8012P4A1C Tastatur 2 × 6 (Variante 2)
F7 = S7 / D7 OUT0 / IN0
Taster F1–F12
ESP32-P4 (Display-Board)
